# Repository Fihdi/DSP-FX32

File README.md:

# DSP-FX32

10hp Digital Multi Effects (Work in Progress)

DSPFX is a digital multi effects module in 10hp. Featuring an ESP32-S3 microcontroller, the module can be freely programmmed with custom firmwares.

# Features

- Stereo Audio in and out
- Changing effects on the fly
- Voltage control over four parameters
- Clock and Gate inputs

# Modes

By pressing the buttons, or sending gate signals to **MODE** and **SUB**, the active digital effect can be changed on the fly.

**MODE** changes what digital effect is active, such as Delay, Reverb, Chorus, etc.

**SUB** changes the sub-mode of the module, such as changing the effect from a "Room Reverb" to "Spring Reverb".

| LED | Mode | PARAM1 | PARAM2 | PARAM3 | MIX | 
| ------------- | ------------- | ------------- | ------------- | ------------- | ------------- |
| 1a | Room Reverb | Time | Feedback Amount | NF | Wet/Dry Mix |
| 1b | Spring Reverb | Time | Feedback Amount | NF | Wet/Dry Mix |
| 2a | Tape Delay | Time | Feedback Amount | NF | Wet/Dry Mix |
| 2b | High Pass Delay | Time | Feedback Amount | NF | Wet/Dry Mix |
| 3 | Chorus | Time | Feedback Amount | NF | Wet/Dry Mix |
| 4 | Flanger | Time | Feedback Amount | NF | Wet/Dry Mix |

# CLK and GATE Input

Sending a clock signal to the **CLK** input overrides the settings of the **PARAM1** knob and CV settings. This allows for effects to be more precisely timed than it would be possible with the knob and CV settings.

The **GATE** input enables/disables a parameter for a given audio effect.

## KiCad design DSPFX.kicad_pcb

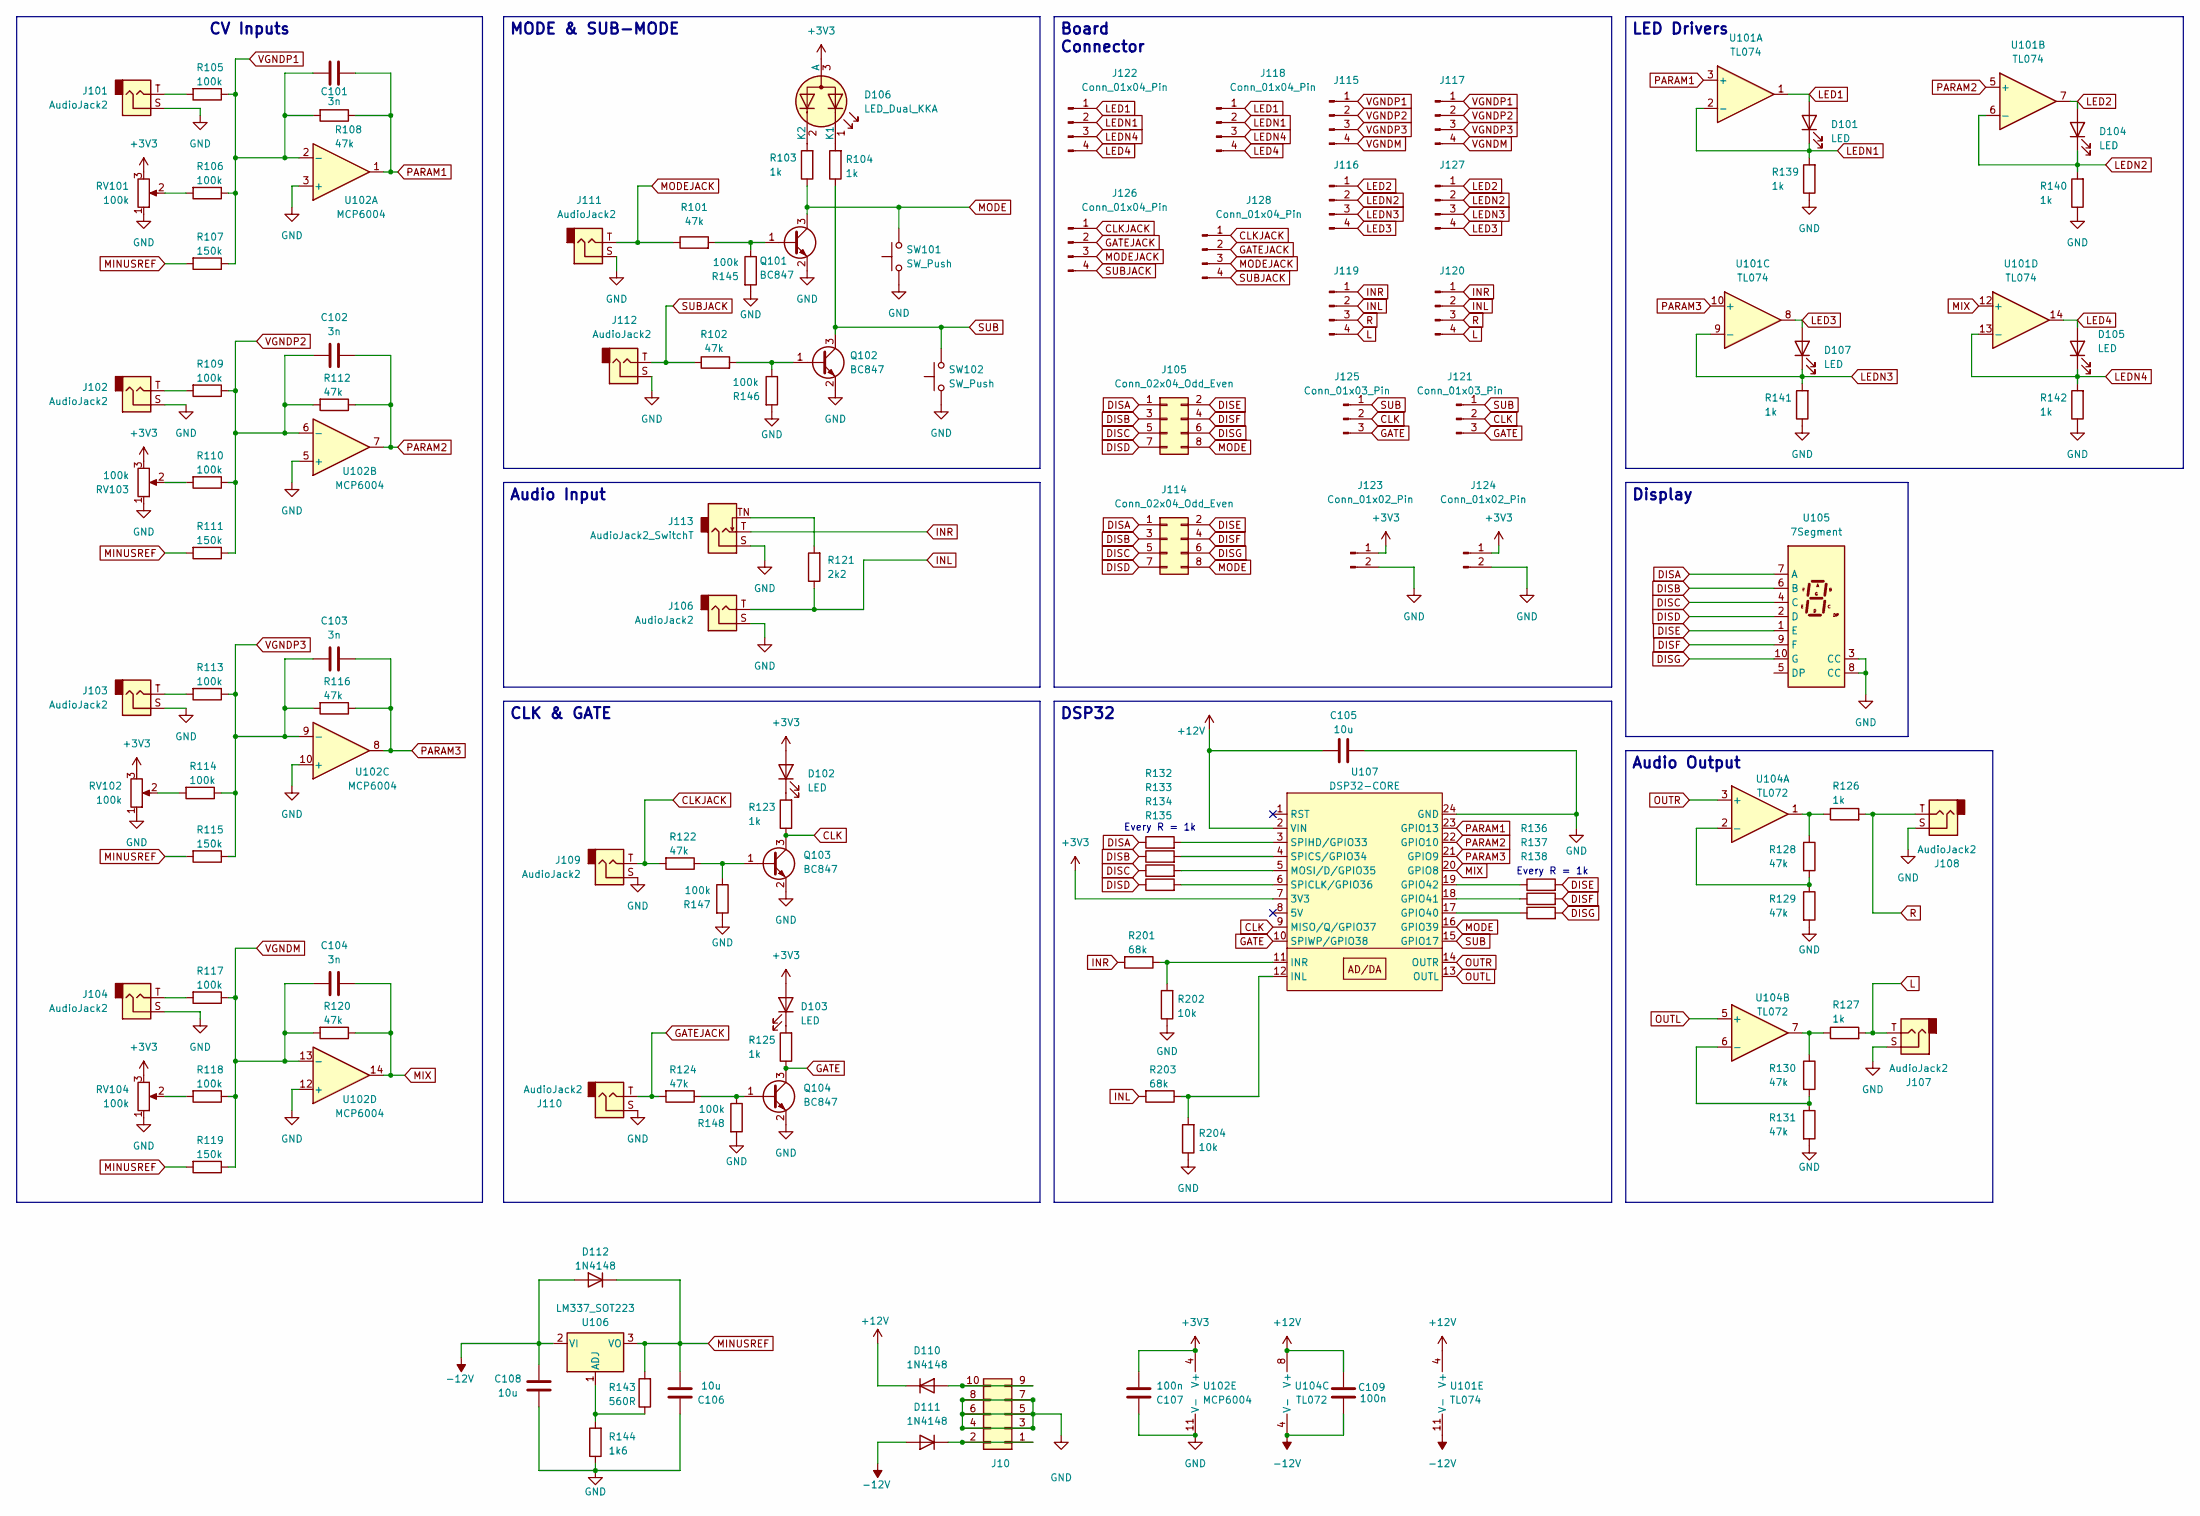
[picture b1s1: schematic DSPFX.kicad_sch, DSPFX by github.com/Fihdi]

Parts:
C101, C102, C103, C104: 3n; C_1206_3216Metric
C105, C106, C108: 10u; C_1206_3216Metric
C107, C109: 100n; C_1206_3216Metric
D101, D102, D103, D104, D105, D107: LED; LED_D3.0mm
D106: LED_Dual_KKA; LED_D5.0mm-3
D110, D111, D112: 1N4148; D_SOD-323_HandSoldering
J10: Conn_02x05_Odd_Even; IDC-Header_2x05_P2.54mm_Vertical
J101, J102, J103, J104, J106, J107, J108, J109, J110, J111, J112: AudioJack2; MonoTRS
J105, J114: Conn_02x04_Odd_Even; PinSocket_2x04_P2.54mm_Vertical
J113: AudioJack2_SwitchT; MonoTRS
J115, J116, J117, J119, J120, J127: Conn_01x04_Pin; PinSocket_1x04_P2.54mm_Vertical
J118, J122, J126, J128: Conn_01x04_Pin; PinHeader_1x04_P2.54mm_Vertical
J121, J125: Conn_01x03_Pin; PinSocket_1x03_P2.54mm_Vertical
J123, J124: Conn_01x02_Pin; PinHeader_1x02_P2.54mm_Vertical
Q101, Q102, Q103, Q104: BC847; SOT-23
R101, R102, R108, R112, R116, R120, R122, R124, R128, R129, R130, R131: 47k; R_1206_3216Metric
R103, R104, R123, R125, R126, R127, R132, R133, R134, R135, R136, R137, R138, R139, R140, R141, R142: 1k; R_1206_3216Metric
R105, R106, R109, R110, R113, R114, R117, R118, R145, R146, R147, R148: 100k; R_1206_3216Metric
R107, R111, R115, R119: 150k; R_1206_3216Metric
R121: 2k2; R_1206_3216Metric
R143: 560R; R_1206_3216Metric
R144: 1k6; R_1206_3216Metric
R201, R203: 68k; R_1206_3216Metric
R202, R204: 10k; R_1206_3216Metric
RV101, RV102, RV103, RV104: 100k; Potentiometer_Alpha_RD901F-40-00D_Single_Vertical
SW101, SW102: SW_Push; PushButton
U101: TL074; SOIC-14_3.9x8.7mm_P1.27mm
U102: MCP6004; SOIC-14_3.9x8.7mm_P1.27mm
U104: TL072; SOIC-8_3.9x4.9mm_P1.27mm
U105: 7Segment; 7SegmentLED_LTS6760_LTS6780
U106: LM337_SOT223; SOT-223-3_TabPin2
U107: DSP32-CORE; ESP32-SEED

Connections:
+3V3: C107.1, D102.2 (A), D103.2 (A), D106.3 (A), J123.1, J124.1, RV101.3, RV102.3, RV103.3, RV104.3, U102.4 (V+), U107.7 (3V3)
+12V: C105.2, C109.2, D110.1 (K), U101.4 (V+), U104.8 (V+), U107.2 (VIN)
-12V: C108.2, C109.1, D111.2 (A), D112.2 (A), U101.11 (V-), U104.4 (V-), U106.2 (VI)
CLK: J121.2, J125.2, Q103.3 (C), R123.1, U107.9 (MISO/Q/GPIO37)
CLKJACK: J109.T, J126.1, J128.1, R122.2
DISA: J105.1, J114.1, R132.1, U105.7 (A)
DISB: J105.3, J114.3, R133.1, U105.6 (B)
DISC: J105.5, J114.5, R134.1, U105.4 (C)
DISD: J105.7, J114.7, R135.1, U105.2 (D)
DISE: J105.2, J114.2, R136.2, U105.1 (E)
DISF: J105.4, J114.4, R137.2, U105.9 (F)
DISG: J105.6, J114.6, R138.2, U105.10 (G)
GATE: J121.3, J125.3, Q104.3 (C), R125.1, U107.10 (SPIWP/GPIO38)
GATEJACK: J110.T, J126.2, J128.2, R124.2
GND: C105.1, C106.2, C107.2, C108.1, J10.3, J10.4, J10.5, J10.6, J10.7, J10.8, J101.S, J102.S, J103.S, J104.S, J106.S, J107.S, J108.S, J109.S, J110.S, J111.S, J112.S, J113.S, J123.2, J124.2, Q101.2 (E), Q102.2 (E), Q103.2 (E), Q104.2 (E), R129.2, R131.2, R139.1, R140.1, R141.1, R142.1, R144.1, R145.2, R146.2, R147.2, R148.2, R202.1, R204.1, RV101.1, RV102.1, RV103.1, RV104.1, SW101.1, SW102.1, U102.3 (+), U102.5 (+), U102.10 (+), U102.11 (V-), U102.12 (+), U105.3 (CC), U105.8 (CC), U107.24 (GND)
INL: J106.T, J119.2, J120.2, R121.1, R203.2
INR: J113.T, J119.1, J120.1, R201.2
L: J107.T, J119.4, J120.4, R127.2
LED1: D101.2 (A), J118.1, J122.1, U101.1
LED2: D104.2 (A), J116.1, J127.1, U101.7
LED3: D107.2 (A), J116.4, J127.4, U101.8
LED4: D105.2 (A), J118.4, J122.4, U101.14
LEDN1: D101.1 (K), J118.2, J122.2, R139.2, U101.2 (-)
LEDN2: D104.1 (K), J116.2, J127.2, R140.2, U101.6 (-)
LEDN3: D107.1 (K), J116.3, J127.3, R141.2, U101.9 (-)
LEDN4: D105.1 (K), J118.3, J122.3, R142.2, U101.13 (-)
MINUSREF: C106.1, D112.1 (K), R107.2, R111.2, R115.2, R119.2, R143.2, U106.3 (VO)
MIX: C104.1, R120.1, U101.12 (+), U102.14, U107.20 (GPIO8)
MODE: J105.8, J114.8, Q101.3 (C), R103.1, SW101.2, U107.16 (GPIO39)
MODEJACK: J111.T, J126.3, J128.3, R101.1
unnamed: D102.1 (K), R123.2
unnamed: D103.1 (K), R125.2
unnamed: D106.1 (K1), R104.2
unnamed: D106.2 (K2), R103.2
unnamed: D110.2 (A), J10.9, J10.10
unnamed: D111.1 (K), J10.1, J10.2
unnamed: J101.T, R105.2
unnamed: J102.T, R109.2
unnamed: J103.T, R113.2
unnamed: J104.T, R117.2
unnamed: J113.TN, R121.2
unnamed: Q101.1 (B), R101.2, R145.1
unnamed: Q102.1 (B), R102.2, R146.1
unnamed: Q103.1 (B), R122.1, R147.1
unnamed: Q104.1 (B), R124.1, R148.1
unnamed: R106.2, RV101.2
unnamed: R110.2, RV103.2
unnamed: R114.2, RV102.2
unnamed: R118.2, RV104.2
unnamed: R126.1, R128.1, U104.1
unnamed: R127.1, R130.1, U104.7
unnamed: R128.2, R129.1, U104.2 (-)
unnamed: R130.2, R131.1, U104.6 (-)
unnamed: R143.1, R144.2, U106.1 (ADJ)
unnamed: R138.1, U107.17 (GPIO40)
unnamed: R137.1, U107.18 (GPIO41)
unnamed: R136.1, U107.19 (GPIO42)
unnamed: R203.1, R204.2, U107.12 (INL)
unnamed: R201.1, R202.2, U107.11 (INR)
unnamed: R134.2, U107.5 (MOSI/D/GPIO35)
unnamed: R135.2, U107.6 (SPICLK/GPIO36)
unnamed: R133.2, U107.4 (SPICS/GPIO34)
unnamed: R132.2, U107.3 (SPIHD/GPIO33)
OUTL: U104.5 (+), U107.13 (OUTL)
OUTR: U104.3 (+), U107.14 (OUTR)
PARAM1: C101.1, R108.1, U101.3 (+), U102.1, U107.23 (GPIO13)
PARAM2: C102.1, R112.1, U101.5 (+), U102.7, U107.22 (GPIO10)
PARAM3: C103.1, R116.1, U101.10 (+), U102.8, U107.21 (GPIO9)
R: J108.T, J119.3, J120.3, R126.2
SUB: J121.1, J125.1, Q102.3 (C), R104.1, SW102.2, U107.15 (GPIO17)
SUBJACK: J112.T, J126.4, J128.4, R102.1
VGNDM: C104.2, J115.4, J117.4, R117.1, R118.1, R119.1, R120.2, U102.13 (-)
VGNDP1: C101.2, J115.1, J117.1, R105.1, R106.1, R107.1, R108.2, U102.2 (-)
VGNDP2: C102.2, J115.2, J117.2, R109.1, R110.1, R111.1, R112.2, U102.6 (-)
VGNDP3: C103.2, J115.3, J117.3, R113.1, R114.1, R115.1, R116.2, U102.9 (-)

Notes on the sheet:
Every R = 1k
MODE & SUB-MODE
Audio Output
CLK & GATE
DSP32
Display
Audio Input
Board Connector
CV Inputs
LED Drivers

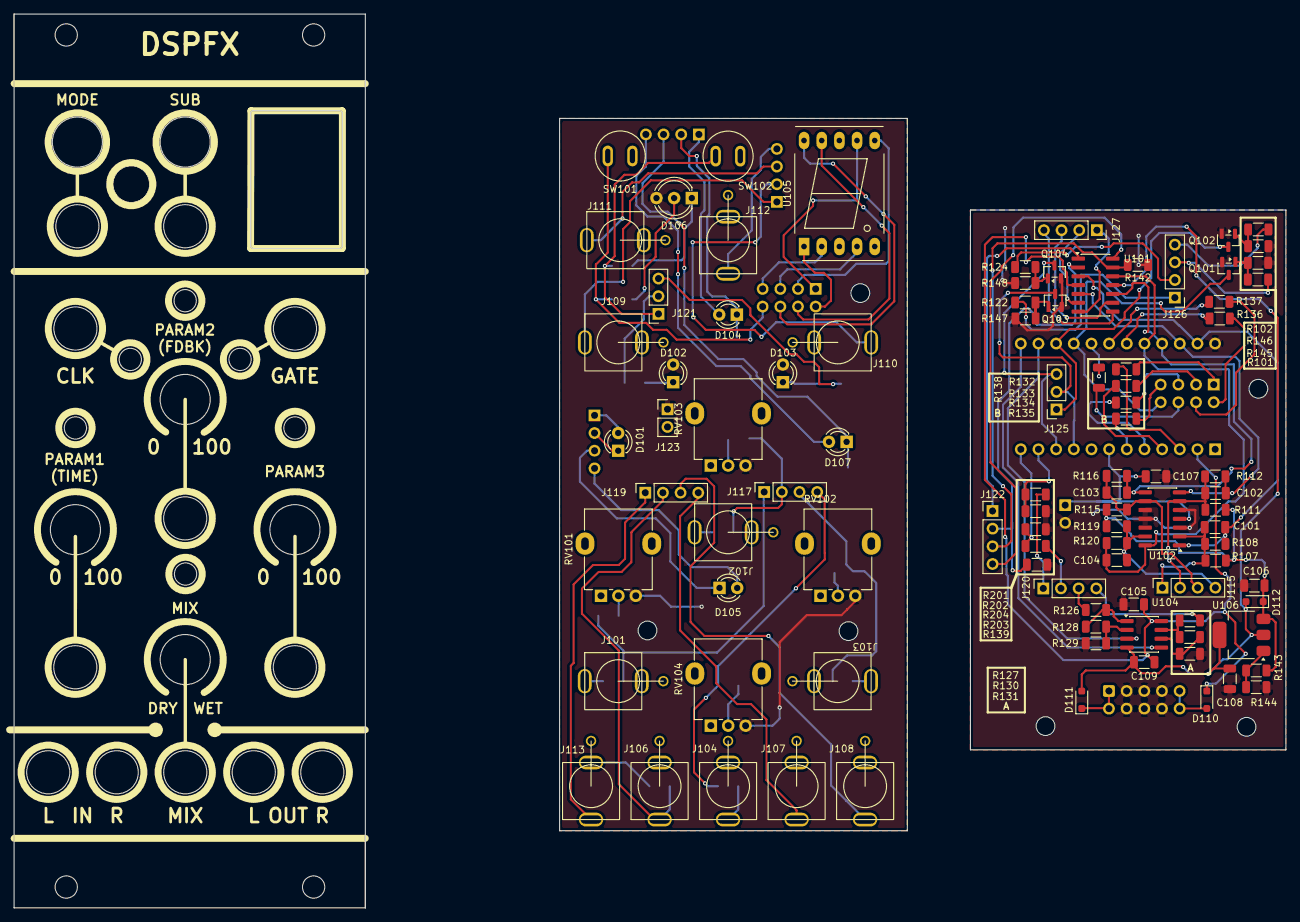
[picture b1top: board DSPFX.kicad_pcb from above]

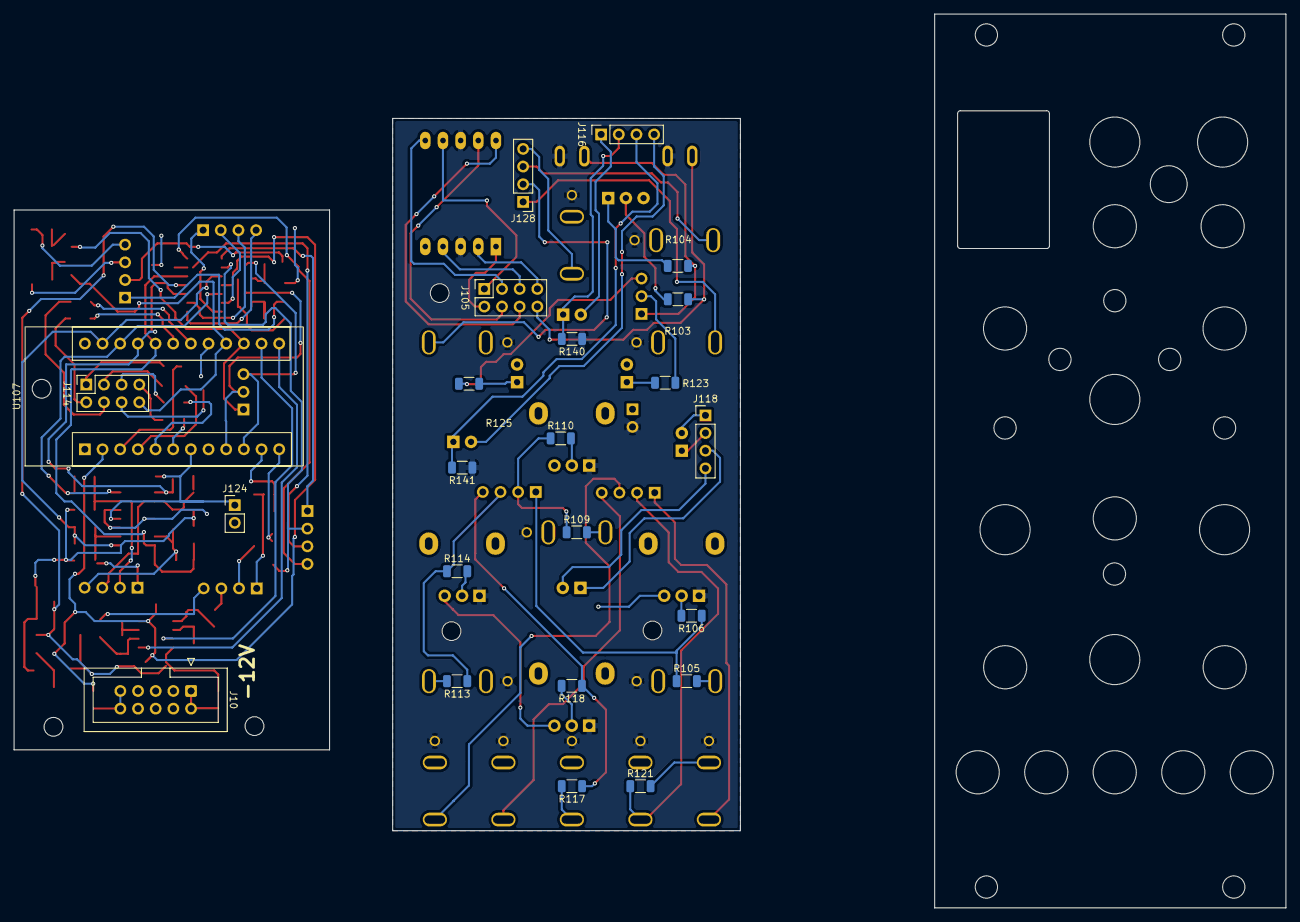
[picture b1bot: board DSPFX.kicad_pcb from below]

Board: 2 copper layers, 182.8 x 128.5 mm, 116 parts (23 on the bottom side), 75 nets.

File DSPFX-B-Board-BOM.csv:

"Reference","Qty","Value","DNP","Exclude from BOM","Exclude from Board","Footprint","Datasheet"
"C101,C102,C103,C104","4","3n","","","","Capacitor_SMD:C_1206_3216Metric","~"
"C105,C106,C108","3","10u","","","","Capacitor_SMD:C_1206_3216Metric","~"
"C107,C109","2","100n","","","","Capacitor_SMD:C_1206_3216Metric","~"
"D110,D111,D112","3","1N4148","","","","Diode_SMD:D_SOD-323_HandSoldering","~"
"J10","1","Conn_02x05_Odd_Even","","","","Connector_IDC:IDC-Header_2x05_P2.54mm_Vertical","~"
"J114","1","Conn_02x04_Odd_Even","","","","Connector_PinSocket_2.54mm:PinSocket_2x04_P2.54mm_Vertical","~"
"J115,J120,J127","3","Conn_01x04_Pin","","","","Connector_PinSocket_2.54mm:PinSocket_1x04_P2.54mm_Vertical","~"
"J122,J126","2","Conn_01x04_Pin","","","","Connector_PinHeader_2.54mm:PinHeader_1x04_P2.54mm_Vertical","~"
"J124","1","Conn_01x02_Pin","","","","Connector_PinHeader_2.54mm:PinHeader_1x02_P2.54mm_Vertical","~"
"J125","1","Conn_01x03_Pin","","","","Connector_PinSocket_2.54mm:PinSocket_1x03_P2.54mm_Vertical","~"
"Q101,Q102,Q103,Q104","4","BC847","","","","Package_TO_SOT_SMD:SOT-23","http://www.infineon.com/dgdl/Infineon-BC847SERIES_BC848SERIE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"
"R101,R102,R108,R112,R116,R120,R122,R124,R128,R129,R130,R131","12","47k","","","","Resistor_SMD:R_1206_3216Metric","~"
"R107,R111,R115,R119","4","150k","","","","Resistor_SMD:R_1206_3216Metric","~"
"R126,R127,R132,R133,R134,R135,R136,R137,R138,R139,R142","11","1k","","","","Resistor_SMD:R_1206_3216Metric","~"
"R143","1","560R","","","","Resistor_SMD:R_1206_3216Metric","~"
"R144","1","1k6","","","","Resistor_SMD:R_1206_3216Metric","~"
"R145,R146,R147,R148","4","100k","","","","Resistor_SMD:R_1206_3216Metric","~"
"R201,R203","2","68k","","","","Resistor_SMD:R_1206_3216Metric","~"
"R202,R204","2","10k","","","","Resistor_SMD:R_1206_3216Metric","~"
"U101","1","TL074","","","","Package_SO:SOIC-14_3.9x8.7mm_P1.27mm","http://www.ti.com/lit/ds/symlink/tl071.pdf"
"U102","1","MCP6004","","","","Package_SO:SOIC-14_3.9x8.7mm_P1.27mm","http://ww1.microchip.com/downloads/en/DeviceDoc/21733j.pdf"
"U104","1","TL072","","","","Package_SO:SOIC-8_3.9x4.9mm_P1.27mm","http://www.ti.com/lit/ds/symlink/tl071.pdf"
"U106","1","LM337_SOT223","","","","Package_TO_SOT_SMD:SOT-223-3_TabPin2","http://www.ti.com/lit/ds/symlink/lm337-n.pdf"
"U107","1","DSP32-CORE","","","","Library:ESP32-SEED",""
